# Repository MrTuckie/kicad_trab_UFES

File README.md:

# kicad_trab_UFES
trabalho de kicad da matéria Exp Graf da Ufes 2017/2 com alb e bob

Acho que acabei tudo aqui. Coloquei a malha de terra.

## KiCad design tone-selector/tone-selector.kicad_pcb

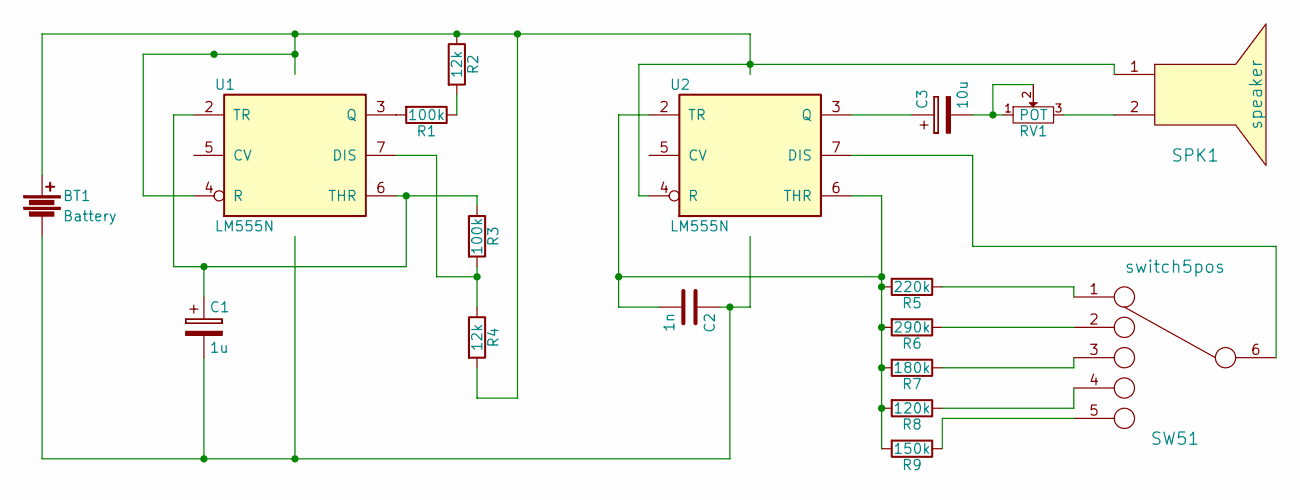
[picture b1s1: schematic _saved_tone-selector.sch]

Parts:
BT1: Battery; PinSocket_1x02_P2.54mm_Vertical
C1: 1u; CP_Radial_D4.0mm_P1.50mm
C2: 1n; C_Disc_D7.0mm_W2.5mm_P5.00mm
C3: 10u; CP_Radial_D5.0mm_P2.00mm
R1, R3: 100k; Resistor_Horizontal_RM7mm
R2, R4: 12k; Resistor_Horizontal_RM7mm
R5: 220k; Resistor_Horizontal_RM7mm
R6: 290k; Resistor_Horizontal_RM7mm
R7: 180k; Resistor_Horizontal_RM7mm
R8: 120k; Resistor_Horizontal_RM7mm
R9: 150k; Resistor_Horizontal_RM7mm
RV1: POT; Potentiometer_WirePads
SPK1: speaker; Pin_Header_Straight_1x02
SW51: switch5pos
U1, U2: LM555N; PDIP-8

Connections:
GND: BT1.2, C1.2, C2.1, U1.1 (GND), U2.1 (GND)
unnamed: C1.1, R3.1, U1.2 (TR), U1.6 (THR)
unnamed: C2.2, R5.2, R6.2, R7.2, R8.2, R9.2, U2.2 (TR), U2.6 (THR)
unnamed: C3.1, U2.3 (Q)
unnamed: C3.2, RV1.1, RV1.2
unnamed: R1.1, R2.2
unnamed: R1.2, U1.3 (Q)
unnamed: R3.2, R4.1, U1.7 (DIS)
unnamed: R5.1, SW51.1
unnamed: R6.1, SW51.2
unnamed: R7.1, SW51.3
unnamed: R8.1, SW51.4
unnamed: R9.1, SW51.5
unnamed: RV1.3, SPK1.2
unnamed: SW51.6, U2.7 (DIS)
VCC: BT1.1, R2.1, R4.2, SPK1.1, U1.4 (R), U1.8 (VCC), U2.4 (R), U2.8 (VCC)

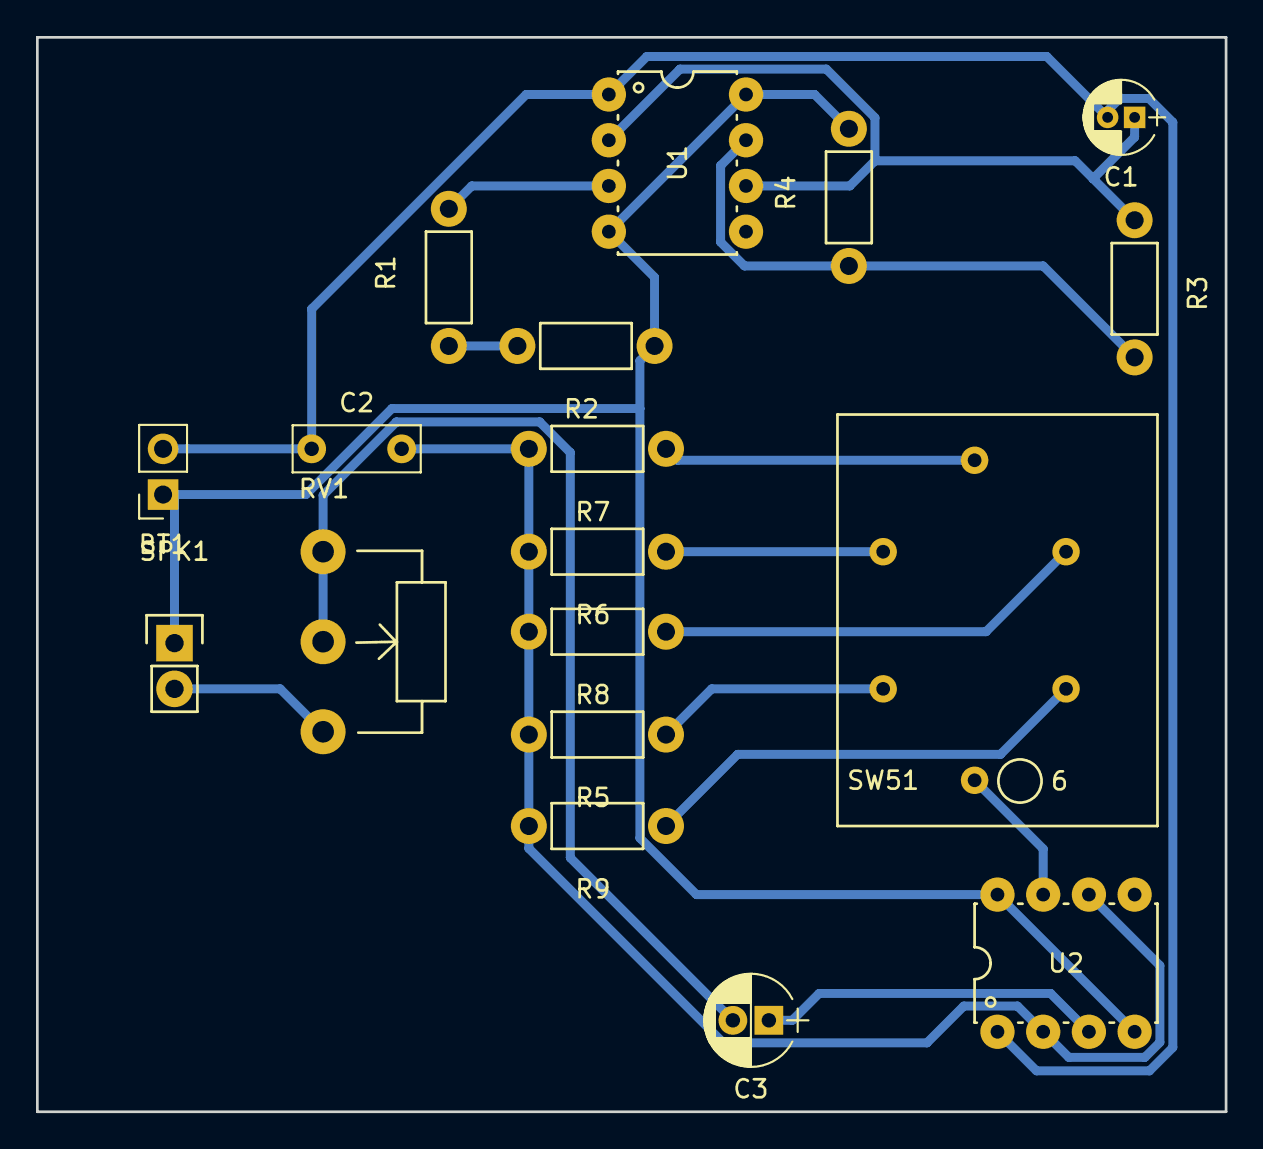
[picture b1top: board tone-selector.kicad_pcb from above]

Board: 2 copper layers, 66.0 x 59.7 mm, 18 parts (0 on the bottom side), 16 nets.

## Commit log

2017-11-30 Eu acho que acabei
    N é possível, tá mto rápido.
2017-11-30 atualizando...
2017-11-30 O problema
2017-11-30 COM MALHA DE TERRAAAAAAAA
2017-11-30 Atualizado com a malha
2017-11-30 atualizado
